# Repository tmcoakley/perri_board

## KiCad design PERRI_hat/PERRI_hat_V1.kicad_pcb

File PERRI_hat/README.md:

# PERRI's Hat (RFSoC Mock) 

V1 &rarr; Version has GND traces in between each via  
V2 &rarr; Version has GND plane attaching to each via  

## To Do: 

- Double check the measurements. They should agree with the [PERRI Board](https://github.com/Payton814/Perri_The_PCB)

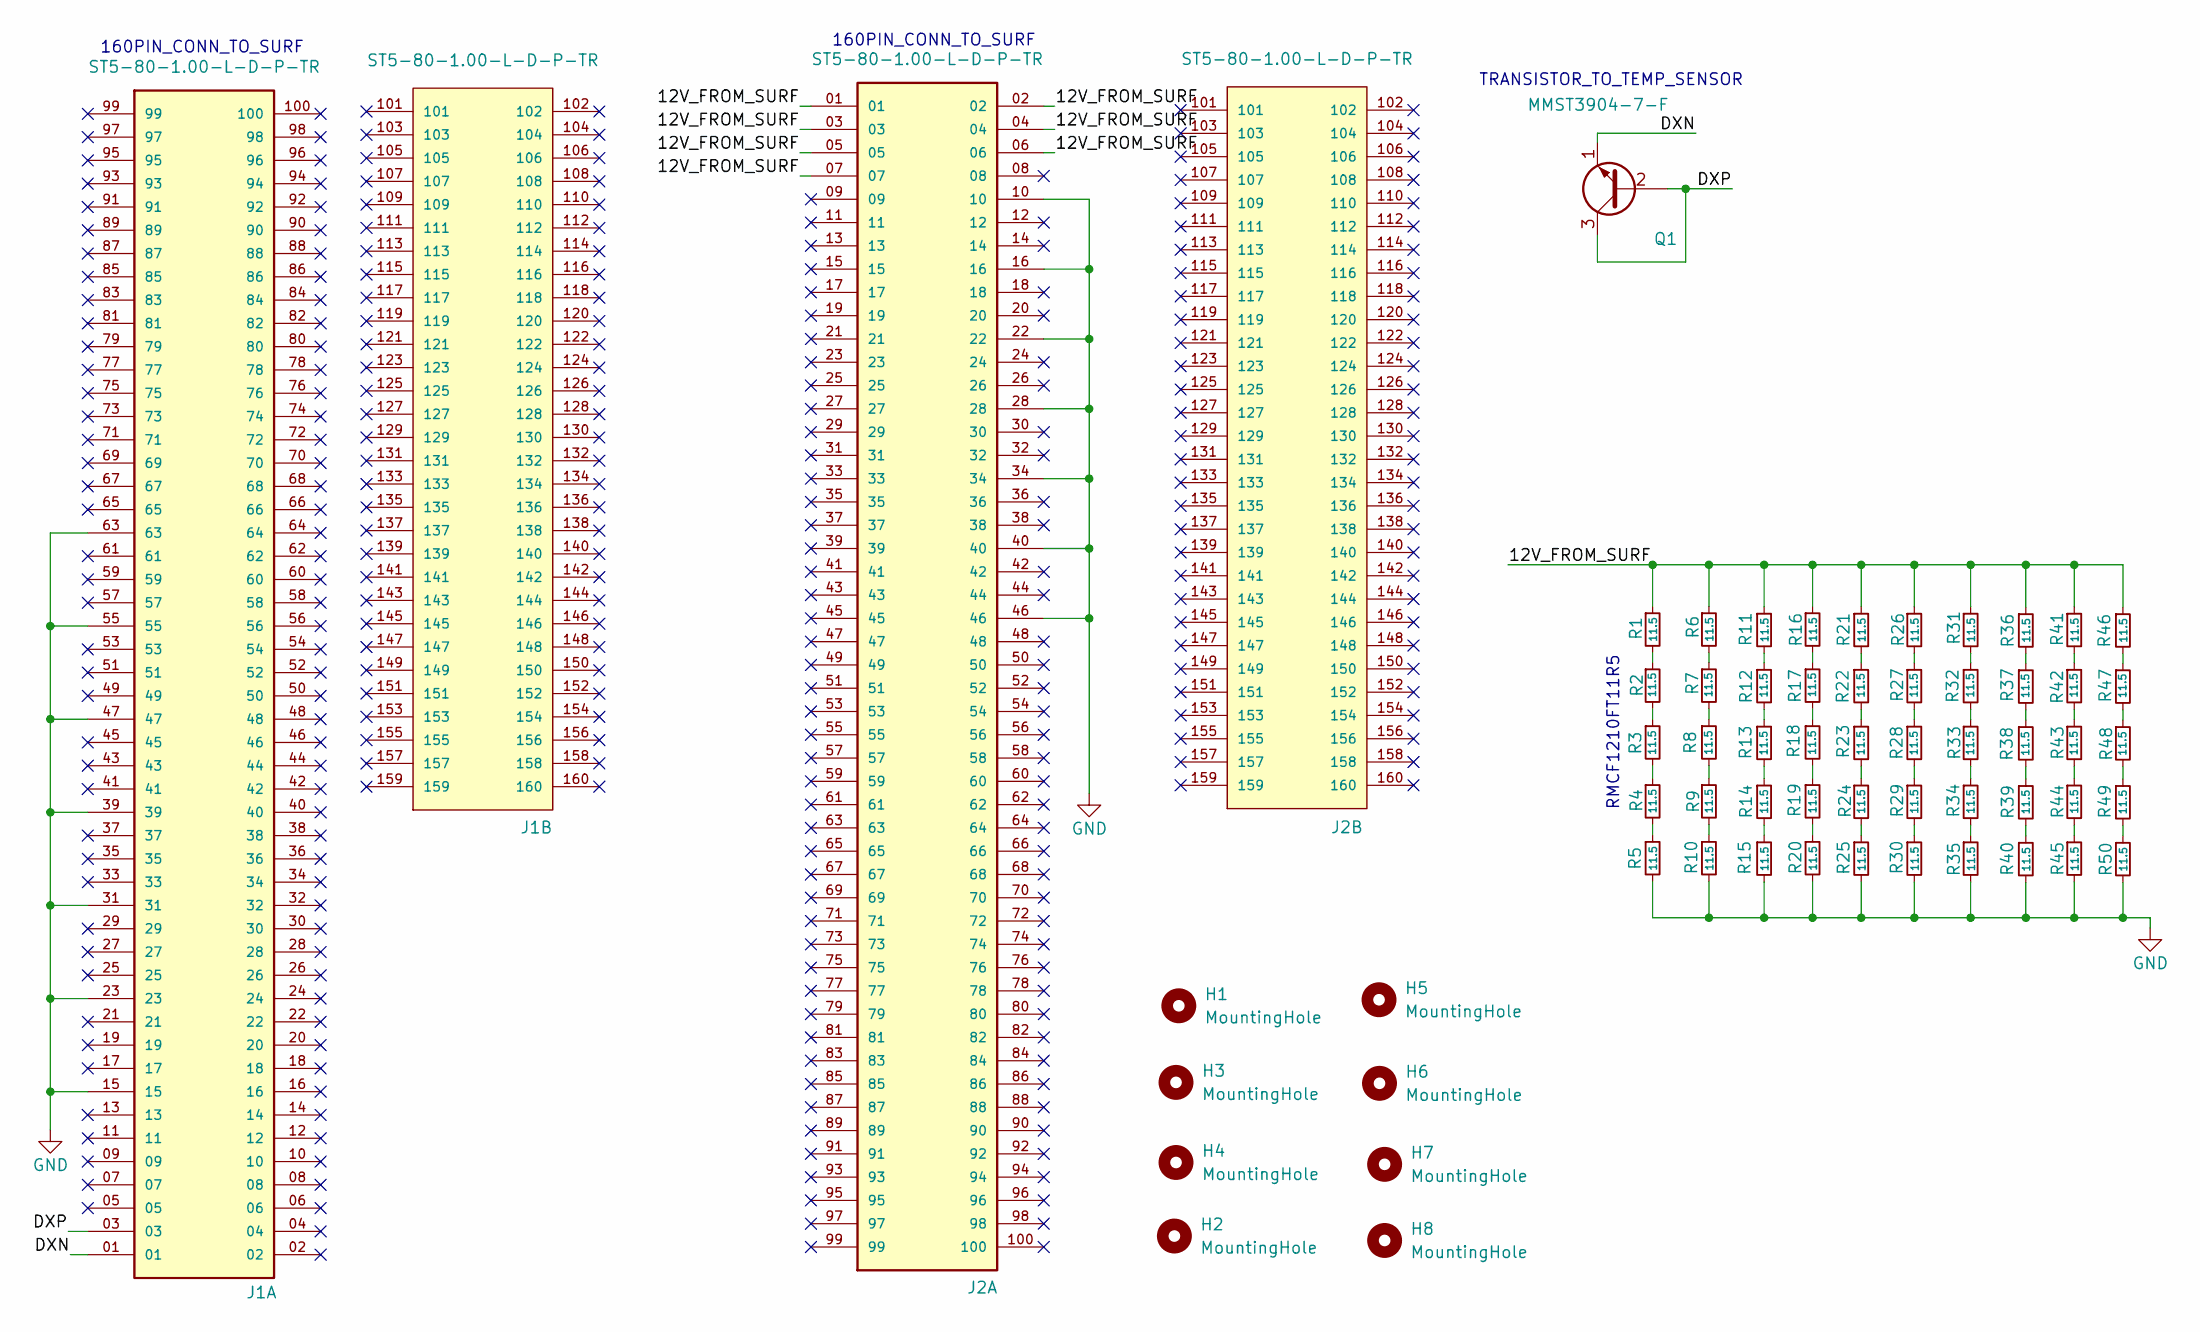
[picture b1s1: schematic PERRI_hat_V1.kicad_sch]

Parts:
H1, H2, H3, H4, H5, H6, H7, H8: MountingHole; Mounting_Hole_for_PERRI
J1, J2: ST5-80-1.00-L-D-P-TR; SAMTEC_ST5-80-1.00-L-D-P-TR; PARTREV G
Q1: MMST3904-7-F
R1, R2, R3, R4, R5, R6, R7, R8, R9, R10, R11, R12, R13, R14, R15, R16, R17, R18, R19, R20, R21, R22, R23, R24, R25, R26, R27, R28, R29, R30, R31, R32, R33, R34, R35, R36, R37, R38, R39, R40, R41, R42, R43, R44, R45, R46, R47, R48, R49, R50: 11.5; R_1210_3225Metric

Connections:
/12V_FROM_SURF: J2.01, J2.02, J2.03, J2.04, J2.05, J2.06, J2.07, J2.09, R1.1, R6.1, R11.1, R16.1, R21.1, R26.1, R31.1, R36.1, R41.1, R46.1
/DXN: J1.01, Q1.1 (E)
/DXP: J1.03, Q1.2 (B), Q1.3 (C)
GND: H1.1, H2.1, H3.1, H4.1, H5.1, H6.1, H7.1, H8.1, J1.15, J1.23, J1.31, J1.39, J1.47, J1.55, J1.63, J2.10, J2.16, J2.22, J2.28, J2.34, J2.40, J2.46, R5.2, R10.2, R15.2, R20.2, R25.2, R30.2, R35.2, R40.2, R45.2, R50.2
unnamed: R1.2, R2.1
unnamed: R2.2, R3.1
unnamed: R3.2, R4.1
unnamed: R4.2, R5.1
unnamed: R6.2, R7.1
unnamed: R7.2, R8.1
unnamed: R8.2, R9.1
unnamed: R9.2, R10.1
unnamed: R11.2, R12.1
unnamed: R12.2, R13.1
unnamed: R13.2, R14.1
unnamed: R14.2, R15.1
unnamed: R16.2, R17.1
unnamed: R17.2, R18.1
unnamed: R18.2, R19.1
unnamed: R19.2, R20.1
unnamed: R21.2, R22.1
unnamed: R22.2, R23.1
unnamed: R23.2, R24.1
unnamed: R24.2, R25.1
unnamed: R26.2, R27.1
unnamed: R27.2, R28.1
unnamed: R28.2, R29.1
unnamed: R29.2, R30.1
unnamed: R31.2, R32.1
unnamed: R32.2, R33.1
unnamed: R33.2, R34.1
unnamed: R34.2, R35.1
unnamed: R36.2, R37.1
unnamed: R37.2, R38.1
unnamed: R38.2, R39.1
unnamed: R39.2, R40.1
unnamed: R41.2, R42.1
unnamed: R42.2, R43.1
unnamed: R43.2, R44.1
unnamed: R44.2, R45.1
unnamed: R46.2, R47.1
unnamed: R47.2, R48.1
unnamed: R48.2, R49.1
unnamed: R49.2, R50.1

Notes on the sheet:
RMCF1210FT11R5
160PIN_CONN_TO_SURF
TRANSISTOR_TO_TEMP_SENSOR

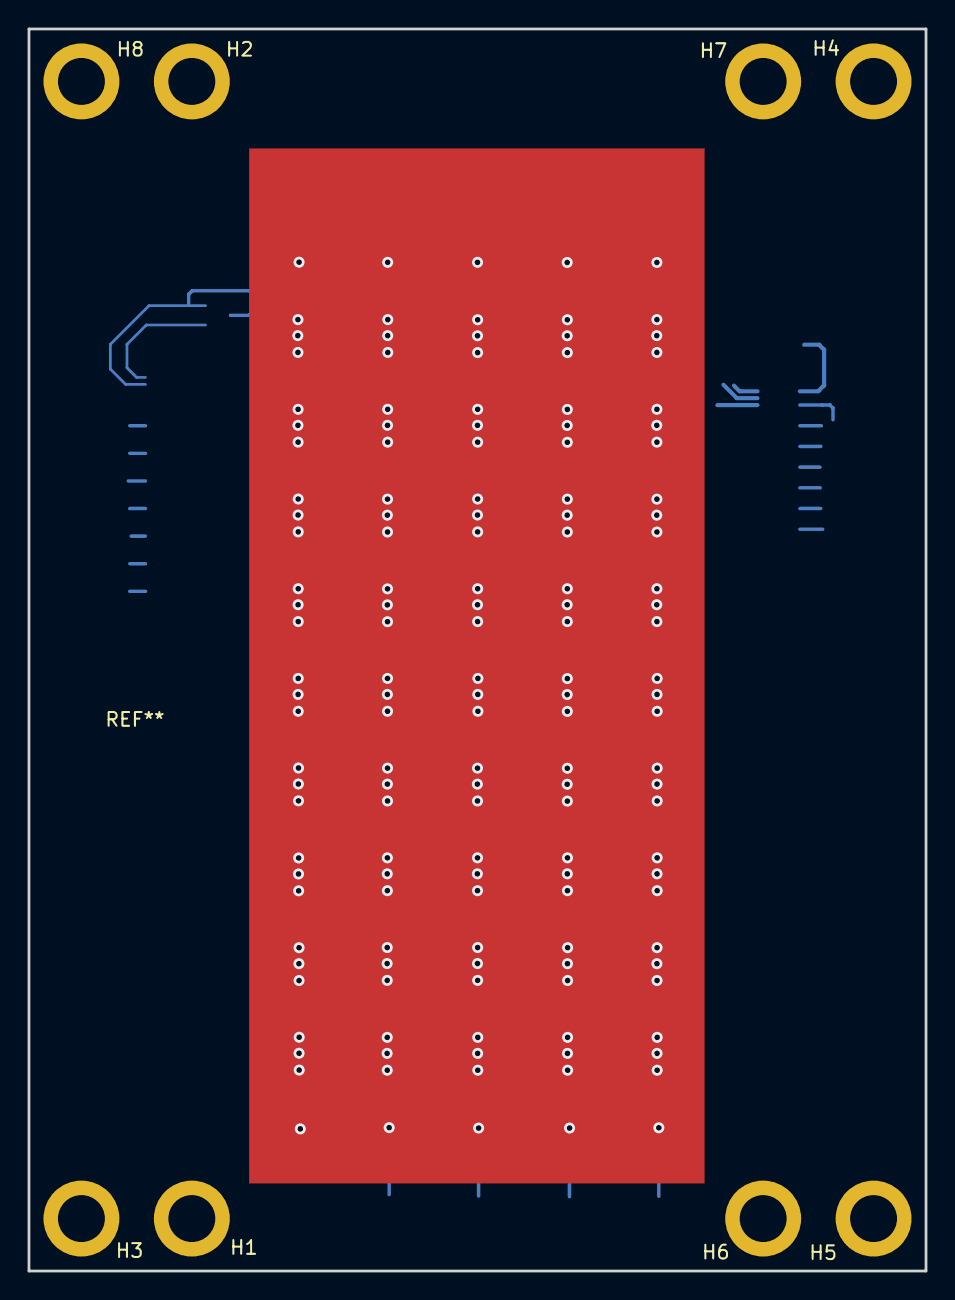
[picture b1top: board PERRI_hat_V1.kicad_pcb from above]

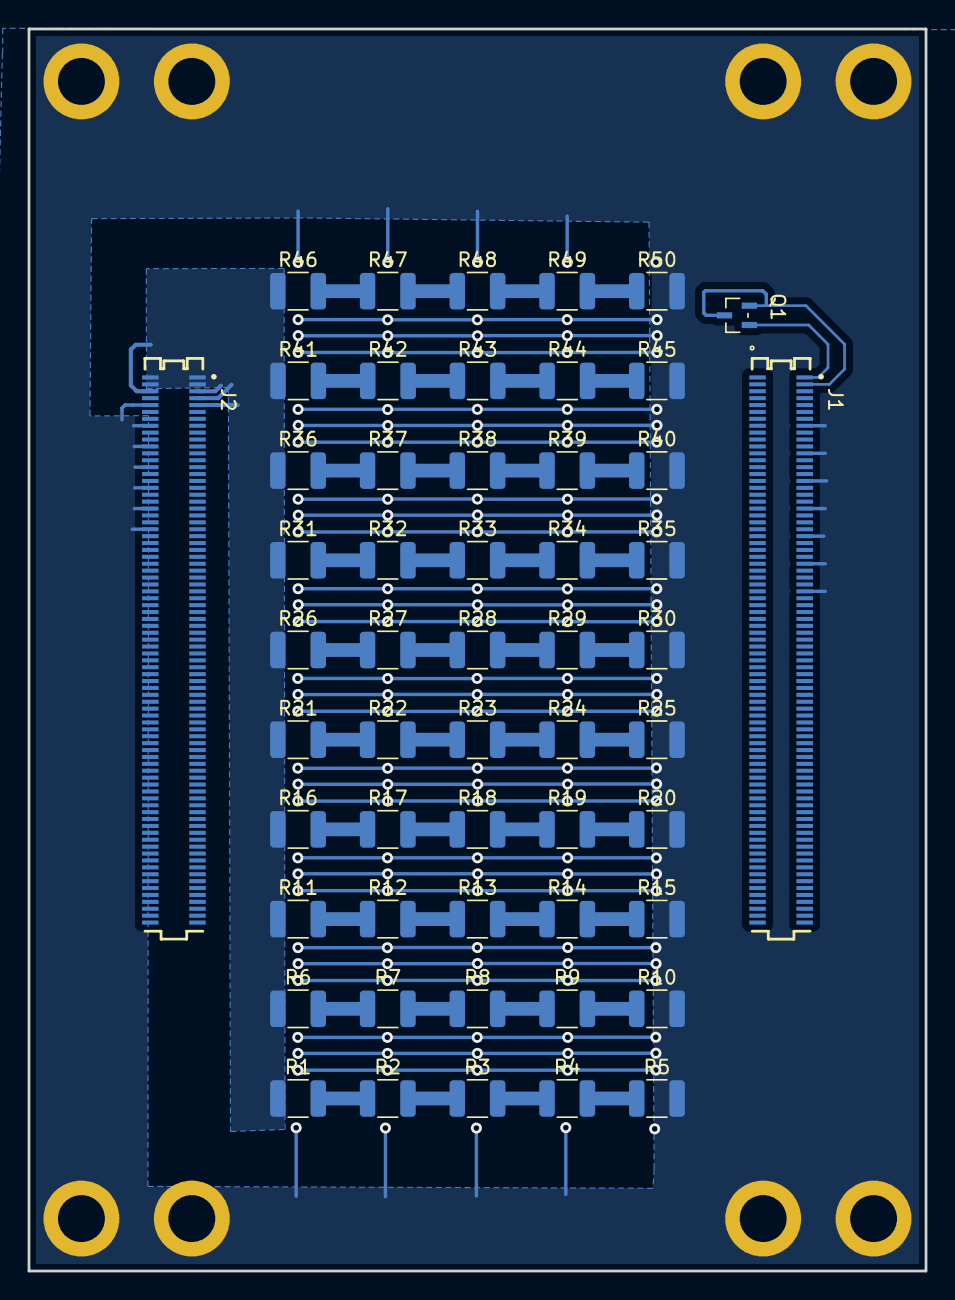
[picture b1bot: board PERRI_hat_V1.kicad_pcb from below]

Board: 2 copper layers, 65.0 x 90.0 mm, 61 parts (53 on the bottom side), 44 nets.

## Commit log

2022-07-05 Rename PERRI_hat/PERRI_hat_footprints.md to PERRI_hat/PERRI_hat_footprints/footprints.md
2022-07-12 fixed issues with layout

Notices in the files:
parts and their libraries:
Copyright 2021 Accelerated Designs. All rights reserved.
